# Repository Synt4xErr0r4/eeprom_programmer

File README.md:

# EEPROM/flash programmer

Ardunio Nano based SST39SF0x0 programmer (so technically flash and not an EEPROM).

Requires two 74x595 (8-bit shift registers; I used 74HC595) as well as three 100nF capacitors (ceramic THT).
For inserting the flash IC, I recommend a ZIF socket (as seen in the image below).

The PCB was designed in KiCAD and manufactured by JLCPCB.

`eeprom_prog.ino` is the firmware for the Arduino Nano and can be compiled and programmed using the Arduino IDE.

`make build` builds the binary (`eeprom_prog.cpp`) for communicating with the Arduino Nano (Linux-only).

use `./eeprom_prog.out read /dev/<DEVICE> <output file path>` to read from the flash
and `./eeprom_prog.out write /dev/<DEVICE> <input file path>` to write to the flash.

I recommend reading again after writing and verifying that the write was actually successful.

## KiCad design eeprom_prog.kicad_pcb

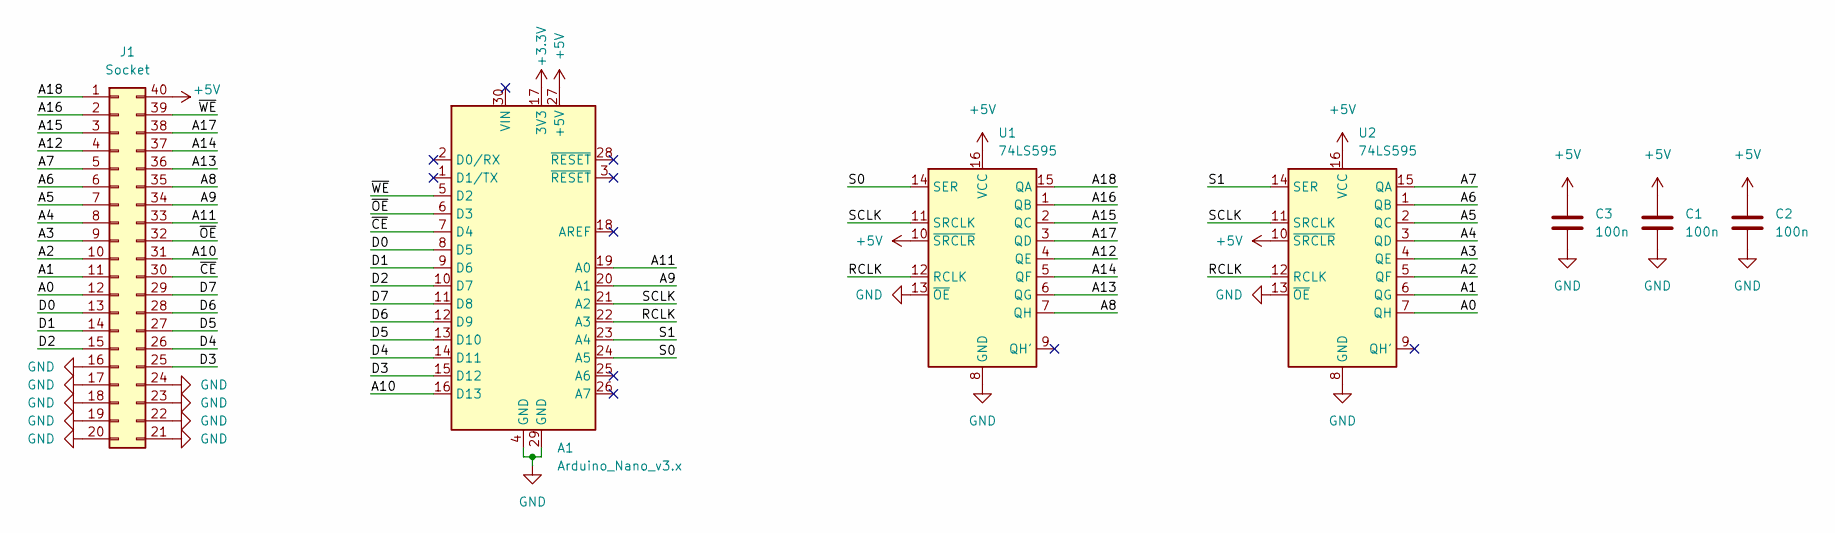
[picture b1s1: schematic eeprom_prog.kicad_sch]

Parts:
A1: Arduino_Nano_v3.x; Arduino_Nano
C1, C2, C3: 100n; C_Disc_D7.5mm_W5.0mm_P5.00mm
J1: Socket; DIP-40_W15.24mm_Socket_LongPads
U1, U2: 74LS595; DIP-16_W7.62mm_LongPads

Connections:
+3.3V: A1.17 (3V3)
+5V: A1.27 (+5V), C1.1, C2.1, C3.1, J1.40, U1.10 (~SRCLR), U1.16 (VCC), U2.10 (~SRCLR), U2.16 (VCC)
/A0: J1.12, U2.7 (QH)
/A1: J1.11, U2.6 (QG)
/A2: J1.10, U2.5 (QF)
/A3: J1.9, U2.4 (QE)
/A4: J1.8, U2.3 (QD)
/A5: J1.7, U2.2 (QC)
/A6: J1.6, U2.1 (QB)
/A7: J1.5, U2.15 (QA)
/A8: J1.35, U1.7 (QH)
/A9: A1.20 (A1), J1.34
/A10: A1.16 (D13), J1.31
/A11: A1.19 (A0), J1.33
/A12: J1.4, U1.4 (QE)
/A13: J1.36, U1.6 (QG)
/A14: J1.37, U1.5 (QF)
/A15: J1.3, U1.2 (QC)
/A16: J1.2, U1.1 (QB)
/A17: J1.38, U1.3 (QD)
/A18: J1.1, U1.15 (QA)
/D0: A1.8 (D5), J1.13
/D1: A1.9 (D6), J1.14
/D2: A1.10 (D7), J1.15
/D3: A1.15 (D12), J1.25
/D4: A1.14 (D11), J1.26
/D5: A1.13 (D10), J1.27
/D6: A1.12 (D9), J1.28
/D7: A1.11 (D8), J1.29
/RCLK: A1.22 (A3), U1.12 (RCLK), U2.12 (RCLK)
/S0: A1.24 (A5), U1.14 (SER)
/S1: A1.23 (A4), U2.14 (SER)
/SCLK: A1.21 (A2), U1.11 (SRCLK), U2.11 (SRCLK)
/~CE: A1.7 (D4), J1.30
/~OE: A1.6 (D3), J1.32
/~WE: A1.5 (D2), J1.39
GND: A1.4 (GND), A1.29 (GND), C1.2, C2.2, C3.2, J1.16, J1.17, J1.18, J1.19, J1.20, J1.21, J1.22, J1.23, J1.24, U1.8 (GND), U1.13 (~OE), U2.8 (GND), U2.13 (~OE)

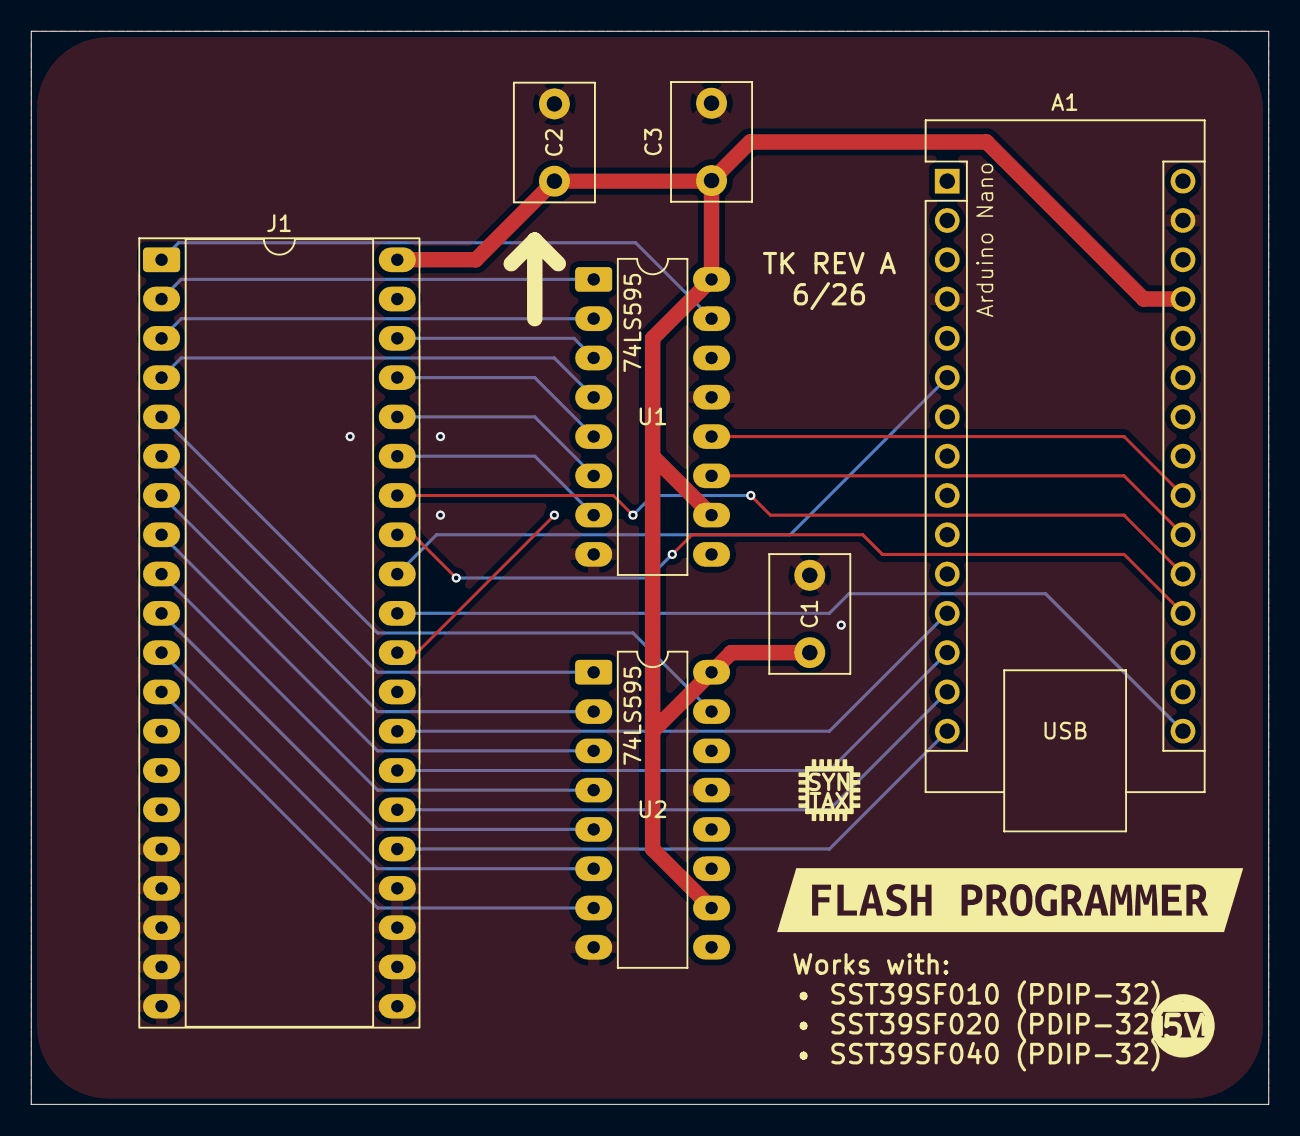
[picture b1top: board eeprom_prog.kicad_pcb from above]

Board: 4 copper layers, 80.0 x 69.4 mm, 8 parts (0 on the bottom side), 36 nets.

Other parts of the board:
kibuzzard-6A224154: G***; kibuzzard-6A224154
